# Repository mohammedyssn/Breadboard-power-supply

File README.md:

# Breadboard power supply

*The 3d view of the PCB*

## Schematic

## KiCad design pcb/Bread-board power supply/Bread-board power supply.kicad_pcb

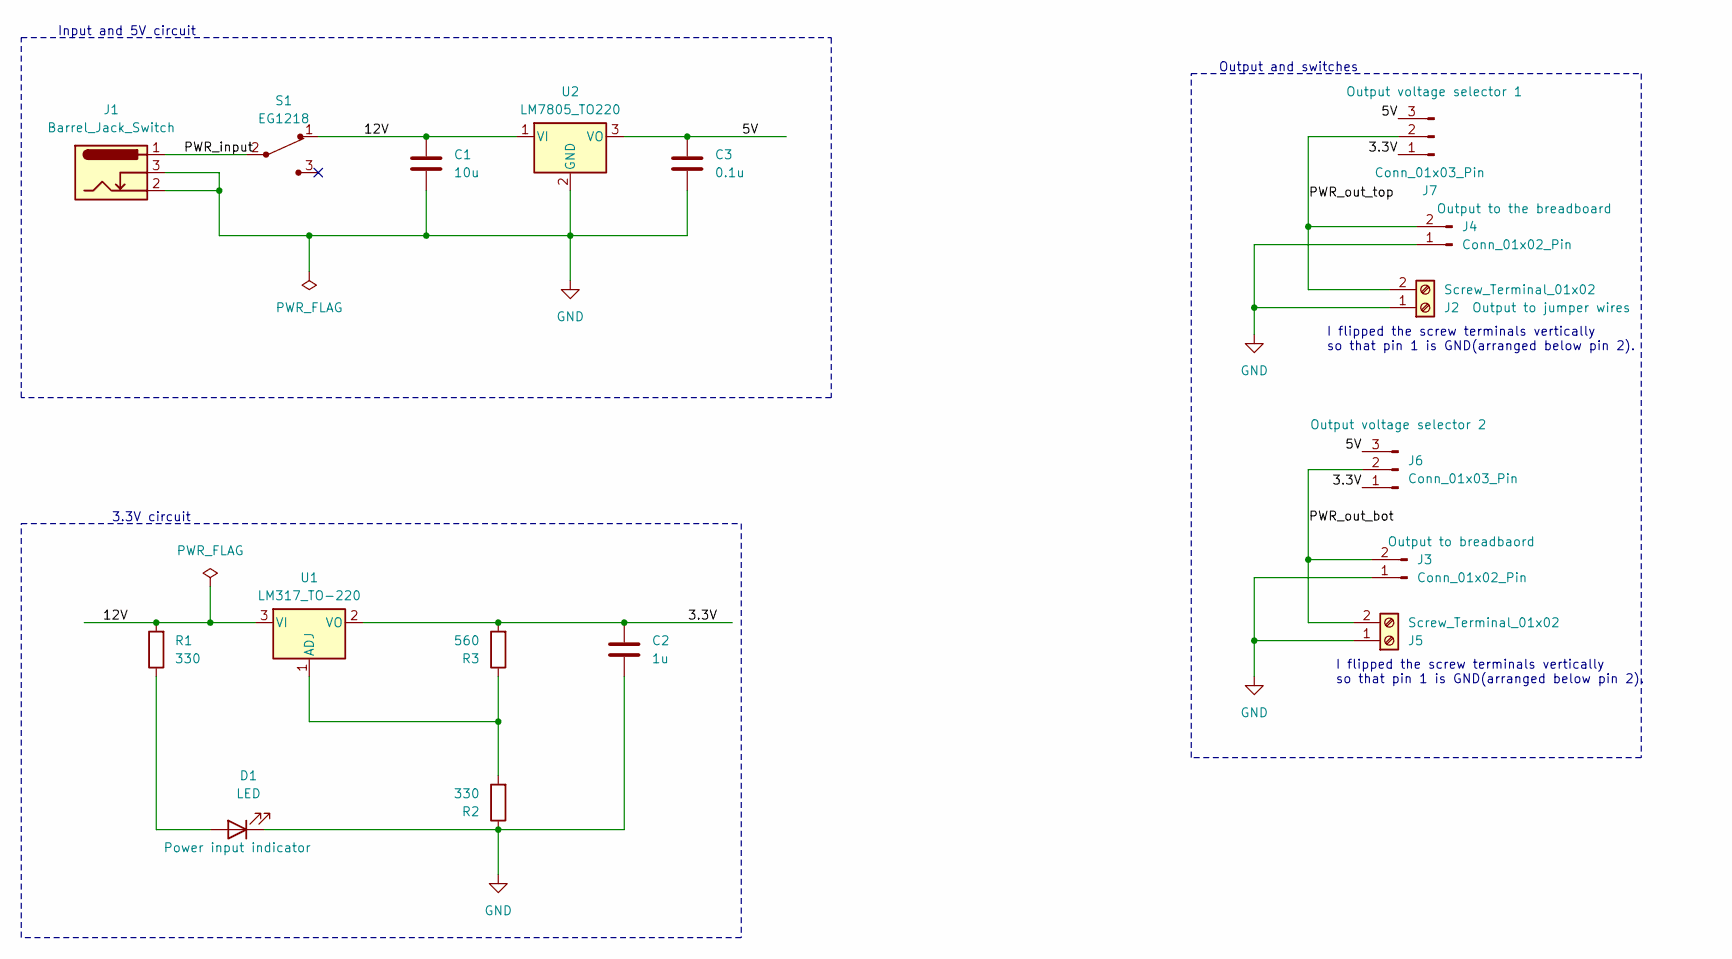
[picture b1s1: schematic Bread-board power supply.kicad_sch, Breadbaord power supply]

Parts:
C1: 10u; C_Disc_D3.0mm_W1.6mm_P2.50mm
C2: 1u; C_Disc_D3.0mm_W1.6mm_P2.50mm
C3: 0.1u; C_Disc_D3.0mm_W1.6mm_P2.50mm
D1: LED; LED_D5.0mm
J1: Barrel_Jack_Switch; BarrelJack_Horizontal
J2, J5: Screw_Terminal_01x02; TerminalBlock_bornier-2_P5.08mm
J3, J4: Conn_01x02_Pin; PinHeader_1x02_P2.54mm_Vertical
J6, J7: Conn_01x03_Pin; PinHeader_1x03_P2.54mm_Vertical
R1, R2: 330; R_Axial_DIN0204_L3.6mm_D1.6mm_P7.62mm_Horizontal
R3: 560; R_Axial_DIN0204_L3.6mm_D1.6mm_P7.62mm_Horizontal
S1: EG1218; Switch_Slide_11.6x4mm_EG1218; MPN EG1218; Digi-Key_PN EG1903-ND
U1: LM317_TO-220; TO-220-3_Vertical
U2: LM7805_TO220; TO-220-3_Vertical

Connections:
/3.3V: C2.1, J6.1, J7.1, R3.2, U1.2 (VO)
/5V: C3.1, J6.3, J7.3, U2.3 (VO)
/12V: C1.1, R1.2, S1.1, U1.3 (VI), U2.1 (VI)
/PWR_input: J1.1, S1.2
/PWR_out_bot: J3.2, J5.2, J6.2
/PWR_out_top: J2.2, J4.2, J7.2; also elsewhere on the board
GND: C1.2, C2.2, C3.2, D1.1 (K), J1.2, J1.3, J2.1, J3.1, J4.1, J5.1, R2.1, U2.2 (GND); also elsewhere on the board
unnamed: D1.2 (A), R1.1
unnamed: R2.2, R3.1, U1.1 (ADJ)

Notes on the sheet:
Output and switches
Input and 5V circuit
I flipped the screw terminals vertically so that pin 1 is GND(arranged below pin 2).
3.3V circuit

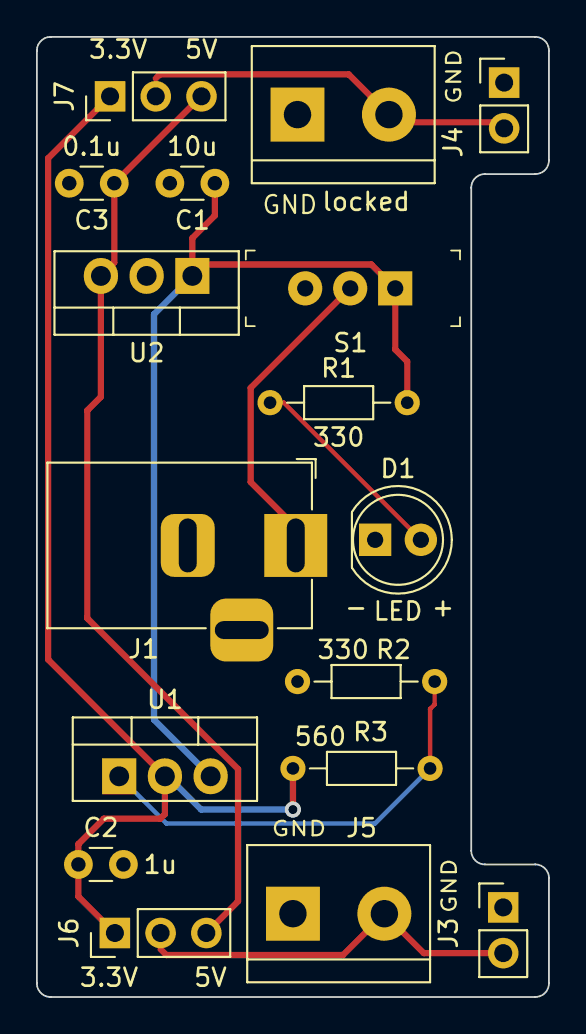
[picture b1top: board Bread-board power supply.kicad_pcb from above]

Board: 2 copper layers, 28.4 x 53.3 mm, 17 parts (0 on the bottom side), 9 nets.

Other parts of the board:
locked: Screw_Terminal_01x02; TerminalBlock_bornier-2_P5.08mm

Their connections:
/PWR_out_top: locked.2; also elsewhere on the board
GND: locked.1; also elsewhere on the board

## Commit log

2023-10-02 Fist Commit
